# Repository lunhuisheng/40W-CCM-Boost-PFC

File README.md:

# 40 W CCM Boost PFC — 设计、仿真与 RevB PCB

面向电源研发岗位展示的学习与工程设计项目。规格：20–28 Vac / 50 Hz 输入，40 V / 1 A / 40 W 输出，50 kHz CCM Boost PFC，平均电流模式双闭环控制。

## 当前状态（2026-10-29）

- 已完成自主行为级 Simulink 模型、组合启动方案、20/24/28 Vac 输入范围及掉电保持时间仿真。
- 已完成 KiCad 原理图及 RevB PCB 的人工器件摆放、手工布线、PGND/AGND 分区覆铜；用户本人完成器件摆放与手工布线，工具用于辅助检查和整理。
- 最新 RevB 静态检查：0 Error、0 Unconnected；34 项 PCB Warning 中 33 项为丝印问题，1 项为已排除检查的 `/RECT_IN` 悬空过孔。H1–H4 是预期的 PCB 专用机械安装孔。详见 [PCB 状态](hardware/REVB_STATUS.md)。
- 制造文件仅作为预览和本地检查材料；尚未完成厂家审图、裸板下单、焊接、上电或实物性能测试。**不要将本仓库作为可直接生产或安全上电的硬件放行包。**

## 最新完整 KiCad 工程

**[打开当前 RevB 完整工程](hardware/latest/)**：用户本人完成布局、手工布线和覆铜的 PCB，配套便于阅读的导线模块化原理图。打开 `hardware/latest/BoostPFC_40W_RevB.kicad_pro`，即可查看两者。旧版文件仍保留供追溯。

## 原理图学习入口

新增 **[10 页中文模块导线图册](hardware/learning/BoostPFC_40W_模块导线学习图册.pdf)**，配套 [KiCad 学习版及核查记录](hardware/learning/)。模块内部用导线表达主要电路路径，238 个引脚网表核对 0 电气差异。

## 仓库内容

| 目录 | 内容 |
|---|---|
| [`hardware/latest/`](hardware/latest/) | 当前主入口：完整手工 PCB + 可读模块化原理图 |
| [`hardware/learning/`](hardware/learning/) | 模块内导线学习原理图、中文图册、核查记录 |
| [`hardware/revb/`](hardware/revb/) | 当前 RevB KiCad 工程、项目本地符号与封装库 |
| [`simulation/BoostPFC_Design/`](simulation/BoostPFC_Design/) | 自主行为级模型、MATLAB 脚本、结构化结果和波形图 |
| [`docs/`](docs/) | 求职快速展示 PDF、项目文档及关键图 |

## 结果边界

仿真指标仅是 **Simulink 行为模型结果**，不代表硬件实测。KiCad ERC/DRC 与本地 CAM 是静态设计/制造检查，不证明效率、功率因数、谐波、温升、开关过冲或 EMI 的硬件表现。原始 `.mat` 波形数据在本地约 887 MB，未纳入本公开仓库；仓库保留测量 JSON、波形图、模型和复现脚本。

## 来源与署名

本项目早期学习参考了 [DeepooBelief/BoostPFC](https://github.com/DeepooBelief/BoostPFC)。本仓库中的 40 W 自主设计、后续控制/启动仿真与 RevB KiCad 工程作为独立作品展示；不声称早期参考工程由本人从零设计。原仓库代码、第三方器件数据手册、厂商模型及其他项目未复制进本仓库。详见 [来源说明](ATTRIBUTION.md)。

## 工程注意事项

在 KiCad 中打开 `hardware/latest/BoostPFC_40W_RevB.kicad_pro`。运行前先核对本地符号、封装映射及原理图网络。当前项目尚处于制造前审查阶段，不应凭 DRC 结果直接制作或上电。

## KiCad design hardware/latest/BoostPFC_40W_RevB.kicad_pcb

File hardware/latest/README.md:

# 当前 RevB 完整工程：手工 PCB + 导线模块化原理图

这是当前推荐打开的完整 KiCad 工程。PCB 保留用户本人完成的器件布局、手工走线、过孔及 PGND/AGND 覆铜；配套原理图采用模块内导线连接、模块间网络标号的阅读方式。

**通过 KiCad 工程管理器打开 `BoostPFC_40W_RevB.kicad_pro`。** 原理图与 PCB 使用同一文件名，均包含在本目录。没有重新摆放器件、重新布线或变更电路。

- [10 页中文模块导线学习图册](BoostPFC_40W_模块导线学习图册.pdf)
- [项目关联与全板焊盘检查](checks/combined_project_check.json)
- [完整 DRC / 原理图一致性](checks/combined_drc.json)
- [ERC](checks/combined_erc.json)

## 最新 PCB

## 配套可读原理图

## 一致性与版本

- PCB：83 个封装、557 段走线、81 个过孔、2 个地覆铜区。PCB SHA-256：`2BB23CBACD7A38E5F8491438F23DFACB0250224D6A2BCA3105C27D4691244414`，与用户手工工程逐字节相同。
- 原理图：仅更改画法和独立项目名；与原 RevB 的 238 个引脚网表 0 电气差异。SCH SHA-256：`5A9EFBDB628A532EC28CAE649ACE53BCD4E28574CD3926B32C63743337EF62EC`。
- 全板 240 个带编号物理焊盘核对：0 网络差异。D1 双阳极=/SW、阴极=/VOUT；R2 Kelvin 和 NT1 关系保持。
- KiCad 10.0.7：DRC 0 Error / 34 个原有 Warning，Unconnected 0。34 项为 15 条丝印重叠、18 条丝印压铜、1 条已排除的旧 RECT_IN 悬空过孔。
- 原理图一致性只有 H1–H4 四个 PCB-only 安装孔提示；ERC 0 Error / 4 个原有库缓存 Warning。

这是当前工程展示与后续编辑的整合副本。历史 `hardware/revb/` 和独立读图 `hardware/learning/` 保留供追溯。制造放行、厂家审图及实物电气验证状态仍需分别确认；本次合并未生成制造文件或执行采购。

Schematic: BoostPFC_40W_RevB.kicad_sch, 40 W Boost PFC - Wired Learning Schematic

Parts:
BR1: GBU6J; Diode_Bridge_Vishay_GBU; MPN GBU6J-E3/45
C1: 2200uF 63V; CP_Radial_D18.0mm_P7.50mm; MPN 63PX2200MEFC18X31.5
C10, C11: 2.2nF; C_0603_1608Metric
C20: 1nF; C_0603_1608Metric
C23, C44: 10nF; C_0603_1608Metric
C24: 100nF U3 LOCAL; C_0603_1608Metric
C25: 100nF U4 LOCAL; C_0603_1608Metric
C30, C41, C42, C43, C46, C48: 100nF; C_0603_1608Metric
C31, C45, C47: 1uF; C_0805_2012Metric
C40: 4.7uF; C_0805_2012Metric
C50: 1uF 25V; C_0805_2012Metric
C51: 4.7uF 10V; C_0805_2012Metric
C61: 100nF U6 LOCAL; C_0603_1608Metric
C62: 100nF U7 LOCAL; C_0603_1608Metric
C63: 100nF U8 LOCAL; C_0603_1608Metric
C64: 100nF U9 LOCAL; C_0603_1608Metric
C65: 100nF RESET EDGE; C_0603_1608Metric
C66: 100nF U10 LOCAL; C_0603_1608Metric
D1: STPST10H100SF; TO-277A; MPN STPST10H100SF
D3: 15V G-S CLAMP; D_SOD-123
D41: 1N4148W FLYBACK; D_SOD-123
D65: BAT54WS RESET CLAMP; D_SOD-323; MPN BAT54WS-7-F
J1: 20-28Vac INPUT; PhoenixContact_MSTBA_2,5_2-G-5,08_1x02_P5.08mm_Horizontal; MPN 1757242
J2: 40V OUTPUT / EXTERNAL LOAD FIXTURE; PhoenixContact_MSTBA_2,5_2-G-5,08_1x02_P5.08mm_Horizontal; MPN 1757242
J3: AUX 12V INPUT; PhoenixContact_MSTBA_2,5_2-G-5,08_1x02_P5.08mm_Horizontal; MPN 1757242
J4: SWD; PinHeader_1x05_P2.54mm_Vertical
K1: G5LE-1 DC12 PRECHARGE BYPASS; Relay_SPDT_Omron-G5LE-1; MPN G5LE-1 DC12
L1: 470uH; Bourns_1140-471K-RC; MPN 1140-471K-RC
NT1: PGND-AGND STAR; NetTie-2_SMD_Pad2.0mm
Q1: IPA052N08NM5S; TO-220-3_Vertical; MPN IPA052N08NM5SXKSA1
Q2: BC817-40; SOT-23; MPN BC817-40,215
R1: 10R 5W PRECHARGE; R_Axial_Power_L20.0mm_W6.4mm_P22.40mm; MPN AC05000001009JAC00
R2: 10mR 1% 4-terminal; Vishay_WSK2512_4Terminal_10mR; MPN WSK2512R0100FEA
R10, R11: 47.5k 0.1%; R_0603_1608Metric
R12: 6.49k 0.1%; R_0603_1608Metric
R13, R14: 56.2k 0.1%; R_0603_1608Metric
R15: 7.50k 0.1%; R_0603_1608Metric
R20, R21: 10R; R_0603_1608Metric
R23: 4.64k 0.1%; R_0603_1608Metric
R24: 10.0k 0.1%; R_0603_1608Metric
R30: 33R; R_0603_1608Metric
R31: 4.7R GATE; R_0603_1608Metric
R32: 10k G-S; R_0603_1608Metric
R33: 10k PWM PULLDOWN; R_0603_1608Metric
R41: 2.2k; R_0603_1608Metric
R51: 100k; R_0603_1608Metric
R61: 10k RESET PULLUP; R_0603_1608Metric
R62: 10k RESET PULSE; R_0603_1608Metric
R63: 1k RESET CLAMP LIMIT; R_0603_1608Metric
SW1: FAULT RESET (MANUAL); SW_PUSH_6mm
TP1: VOUT TEST; TestPoint_Loop_D2.50mm_Drill1.0mm
TP2: PGND TEST; TestPoint_Loop_D2.50mm_Drill1.0mm
TP3: RECT_RAW TEST; TestPoint_Loop_D2.50mm_Drill1.0mm
TP4: ISENSE_ADC TEST; TestPoint_Loop_D2.50mm_Drill1.0mm
TP5: OC_RAW TEST; TestPoint_Loop_D2.50mm_Drill1.0mm
TP6: GATE_Q1 TEST; TestPoint_Loop_D2.50mm_Drill1.0mm
TP7: AGND TEST; TestPoint_Loop_D2.50mm_Drill1.0mm
U1: STM32G431CBT6; LQFP-48_7x7mm_P0.5mm; MPN STM32G431CBT6
U2: UCC27517ADBVR; SOT-23-5; MPN UCC27517ADBVR
U3: INA180A2IDBVR; SOT-23-5; MPN INA180A2IDBVR
U4: TLV3201AIDBVR; SOT-23-5; MPN TLV3201AIDBVR
U5: TPS7A2433DBVR; SOT-23-5; MPN TPS7A2433DBVR
U6: SN74LVC1G74DCUR; VSSOP-8_2.3x2mm_P0.5mm; MPN SN74LVC1G74DCUR
U7, U9: SN74LVC1G32DBVR; SOT-23-5; MPN SN74LVC1G32DBVR
U8: TPS3839K33DBZT; SOT-23; MPN TPS3839K33DBZT
U10: SN74LVC1G17DBVR; SOT-23-5; MPN SN74LVC1G17DBVR

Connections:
/+3V3: C24.1, C25.1, C40.1, C41.1, C42.1, C43.1, C44.1, C45.1, C46.1, C47.1, C48.1, C51.1, C61.1, C62.1, C63.1, C64.1, C66.1, D65.1 (K), J4.1, R23.1, R61.1, R62.1, U1.1 (VBAT), U1.20 (VREF+), U1.21 (VDDA), U1.24 (VDD), U1.36 (VDD), U1.48 (VDD), U3.5 (V+), U4.5 (VCC), U5.5 (OUT), U6.2 (D), U6.8 (VCC), U7.5 (VCC), U8.3 (VDD), U9.5 (VCC), U10.5 (VCC)
/+12V: C30.1, C31.1, C50.1, D41.1 (K), J3.1, K1.5, U2.1 (VDD), U5.1 (IN), U5.3 (EN)
/AC_IN_A: BR1.3, J1.1
/AC_IN_B: BR1.2, J1.2
/AGND: C10.2, C11.2, C23.2, C24.2, C25.2, C40.2, C41.2, C42.2, C43.2, C44.2, C45.2, C46.2, C47.2, C48.2, C50.2, C51.2, C61.2, C62.2, C63.2, C64.2, C66.2, J3.2, J4.5, NT1.2, Q2.2 (E), R12.2, R15.2, R24.2, R51.2, SW1.2, TP7.1, U1.19 (VSSA), U1.23 (VSS), U1.35 (VSS), U1.47 (VSS), U3.2 (GND), U4.2 (GND), U5.2 (GND), U6.4 (GND), U7.3 (GND), U8.1 (GND), U9.3 (GND), U10.3 (GND)
/BRIDGE_NEG: BR1.4 (-), R2.2 (PWR-)
/DRIVER_DISABLE: U2.4 (IN-), U7.4 (Y)
/FAULT_LATCHED: U1.17 (PB1), U6.5 (Q), U7.2 (B)
/GATE_DRV: R31.1, U2.5 (OUT)
/GATE_Q1: D3.1 (K), Q1.1 (G), R31.2, R32.1, TP6.1
/INA_N: C20.2, R21.2, U3.4 (-)
/INA_P: C20.1, R20.2, U3.3 (+)
/ISENSE_ADC: TP4.1, U1.8 (PA0), U3.1, U4.3 (+)
/ISENSE_N: R2.4 (SENSE-), R21.1
/ISENSE_P: R2.3 (SENSE+), R20.1
/K1_COIL_L: D41.2 (A), K1.2, Q2.3 (C)
/K1_COIL_L_DRV: Q2.1 (B), R41.2, R51.1
/NRST: J4.4, U1.7 (NRST)
/OCP_CLEAR_N: U6.6 (~CLR), U9.4 (Y)
/OCP_REF: C23.1, R23.2, R24.1, U4.4 (-)
/OC_RAW: TP5.1, U1.16 (PB0), U4.1 (OUT), U6.1 (CLK), U7.1 (A), U9.2 (B)
/PGND: C1.2, C30.2, C31.2, D3.2 (A), J2.2, NT1.1, Q1.3 (S), R2.1 (PWR+), R32.2, R33.2, TP2.1, U2.2 (GND)
/POR_PRE_N: U6.7 (~PRE), U8.2 (~RESET)
/PRECHARGE_BYPASS_CMD: R41.1, U1.43 (PB6)
/PWM_CMD: R30.1, U1.30 (PA8)
/PWM_DRV: R30.2, R33.1, U2.3 (IN+)
/RECT_IN: K1.3, L1.1, R1.2
/RECT_RAW: BR1.1 (+), K1.1, R1.1, R13.1, TP3.1
/RESET_BUTTON_N: C65.1, R61.2, SW1.1
/RESET_EDGE: C65.2, R63.1
/RESET_PULSE_N: U9.1 (A), U10.4 (Y)
/RESET_PULSE_RC: D65.2 (A), R62.2, R63.2, U10.2 (A)
/SW: D1.1 (A), D1.2 (A), L1.2, Q1.2 (D)
/SWCLK: J4.3, U1.38 (PA14)
/SWDIO: J4.2, U1.37 (PA13)
/VOUT: C1.1, D1.3 (K), J2.1, R10.1, TP1.1
/VOUT_DIV: R10.2, R11.1
/VOUT_SENSE: C10.1, R11.2, R12.1, U1.9 (PA1)
/VRECT_DIV: R13.2, R14.1
/VRECT_SENSE: C11.1, R14.2, R15.1, U1.10 (PA2)

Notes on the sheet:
40 W CCM BOOST PFC | WIRED MODULAR LEARNING SCHEMATIC
Read the energy flow first (01 -> 02), then driver (03), sensing (04-06), fault logic (07), and MCU (08).
Same RevB circuit. Internal functional paths use wires. Matching port labels connect between modules; crossing wires have no implicit connection.
01 AC INPUT / RECTIFIER / PRECHARGE
J1 -> BR1 -> R1; K1 bypasses R1 after precharge
02 BOOST POWER STAGE
L1 -> SW -> D1 -> C1 / J2; Q1 and R2 complete the return
03 MOSFET GATE DRIVER
PWM_CMD -> R30 -> U2 -> R31 -> GATE_Q1
04 KELVIN CURRENT SENSE
R2 sense terminals -> R20 / R21 -> U3 -> ISENSE_ADC
05 VOLTAGE SENSE
Two separate resistor dividers: VOUT and RECT_RAW
06 HARDWARE OVERCURRENT
U4 compares ISENSE_ADC with OCP_REF
09 AUXILIARY POWER
J3 12 V auxiliary input -> U5 -> +3V3
07 FAULT LATCH / POR / MANUAL RESET
OC_RAW -> latch + fast OR -> DRIVER_DISABLE; no MCU clear
08 STM32 CONTROL / SWD / DECOUPLING
Digital control interface; all existing supply and NC connections retained
10 GROUND STAR / TEST POINTS
NT1 is the intended PGND / AGND connection; TP1-TP7 observe nets
K1 coil path is wired to Q2 and D41; its contact path bypasses R1.
R2 pins 1/2: power return. Pins 3/4: independent Kelvin outputs to Module 04.
IN- receives DRIVER_DISABLE. R33 is the existing hardware PWM pulldown.
C20 is between INA_P and INA_N, not an input-to-ground capacitor.
VOUT -> R10/R11/R12
RECT_RAW -> R13/R14/R15
OC_RAW is an independent hardware shutdown input to Module 07.
Manual reset edge -> RC/clamp -> Schmitt U10 -> OR U9 -> latch CLR.
4.7 uF bulk
VDD24 / VSS23
VDD36 / VSS35
VDD48 / VSS47
VDDA21 / VSSA19
VREF+20 / VSSA19
VBAT1 / AGND
The existing circuit directly shares +3V3 and AGND for these pins; no new filter has been added.
MCU calculates digital PI / current reference / PWM. Fault status is read-only.

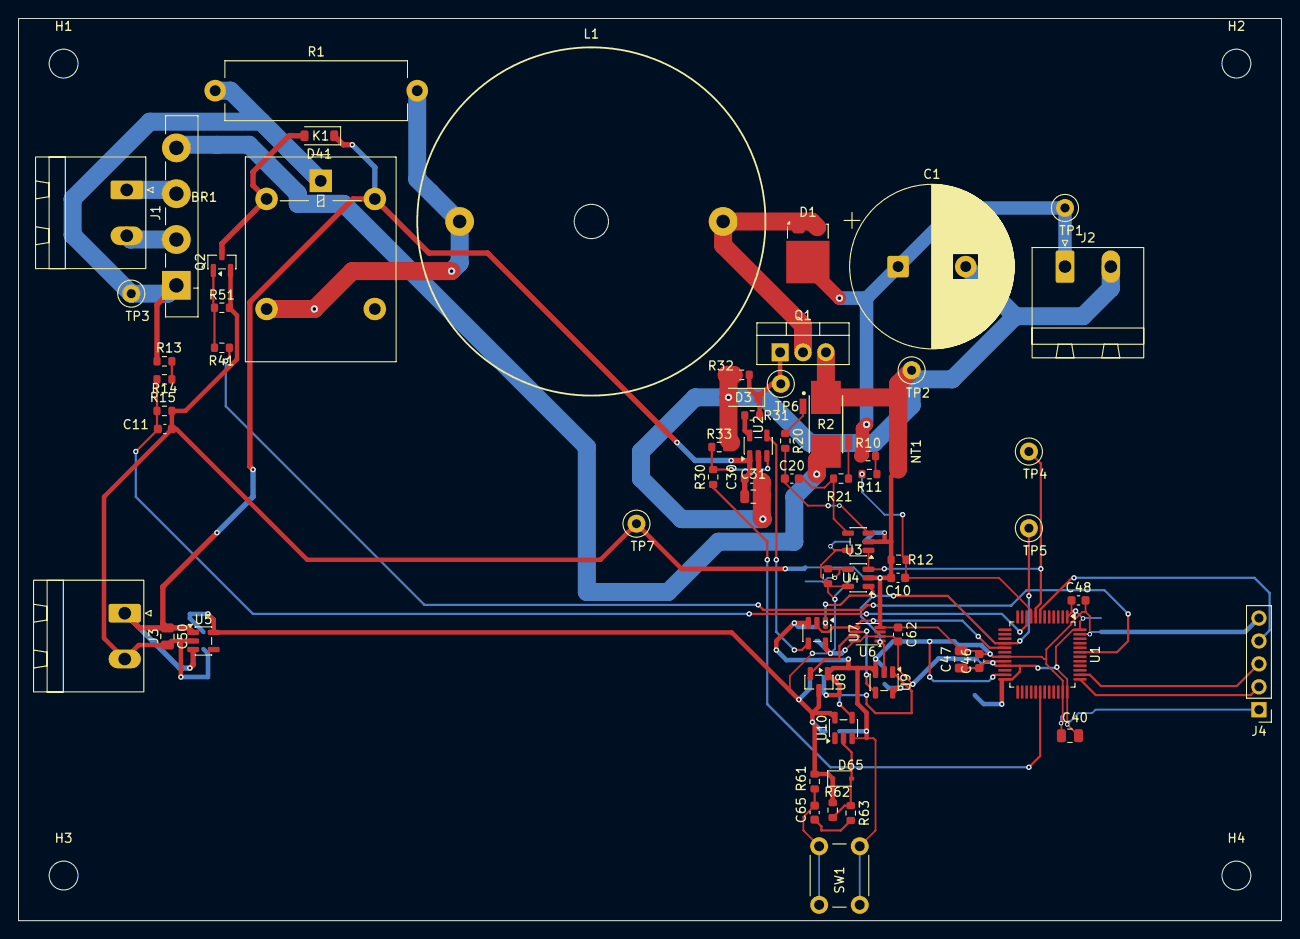
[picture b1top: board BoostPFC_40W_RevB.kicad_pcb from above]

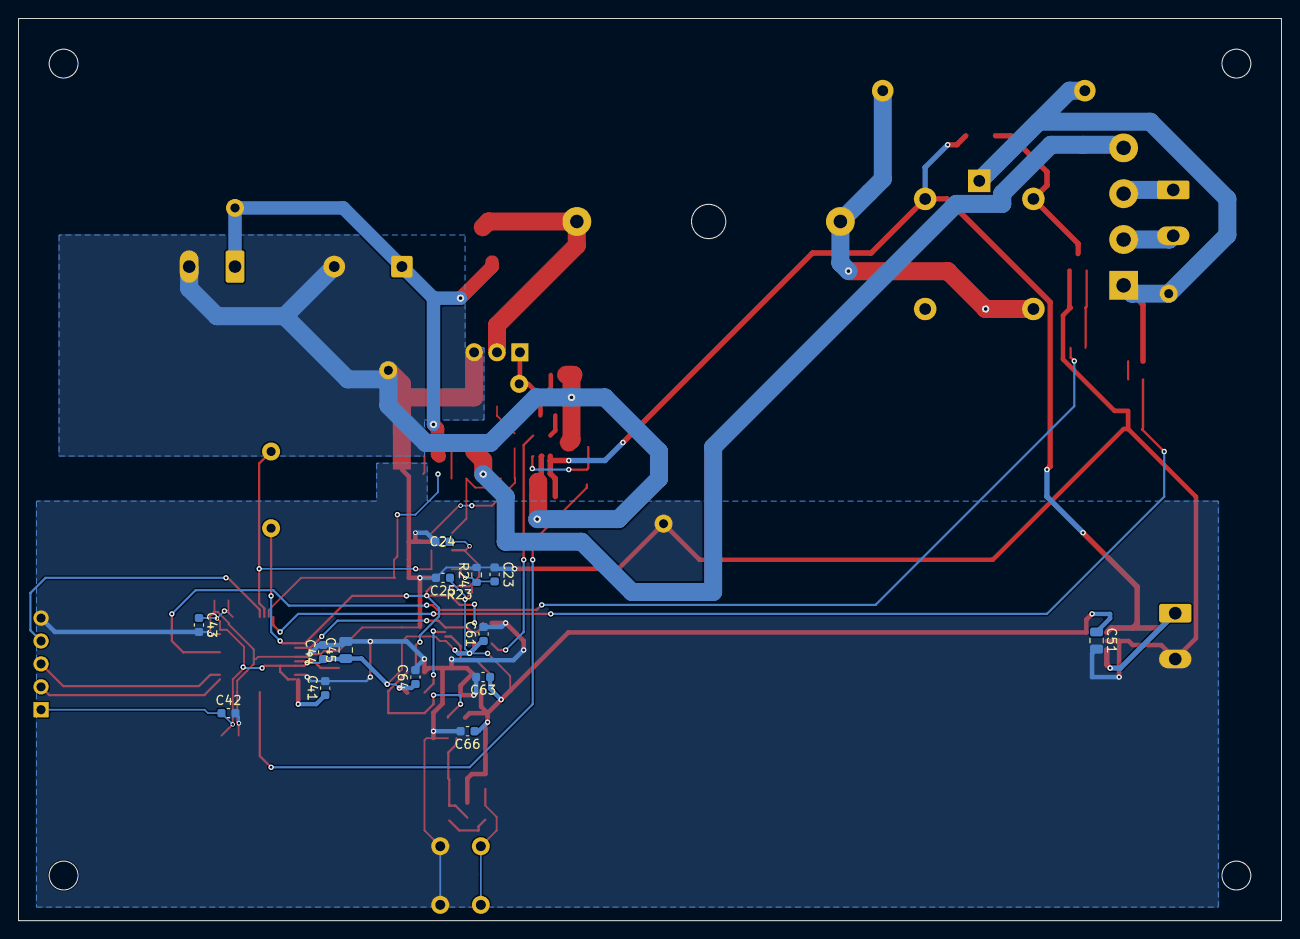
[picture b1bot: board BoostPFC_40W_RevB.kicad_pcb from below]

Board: 2 copper layers, 140.0 x 100.0 mm, 83 parts (14 on the bottom side), 40 nets.

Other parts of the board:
H1, H2, H3, H4: M3 mounting hole; MountingHole_3.2mm_M3
